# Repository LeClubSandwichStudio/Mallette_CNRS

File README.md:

# Mallette_CNRS
Water Analyser Briefcase for scientist
> ### Description

> ### [3D View](https://a360.co/3F3qp8W) - models designed by Mathorel Remi (2021)

# Key Features
> ### Hardware

* Protection Case : 
  * Case : [Pelican 1200](https://www.pelican.com/us/en/product/cases/protector/1200) 
  * Panel Frame : [Pelican 1200PF](https://www.pelican.com/us/en/accessory/cases/special-application-panel-frame/1200pf)
* MCU : [Teensy 3.6](https://www.pjrc.com/store/teensy36.html)
* OS : Raspberry Pi 4B - [RaspOS](https://www.raspberrypi.org/software/)
* Sensors : 
  * PH : [SEN0161-V2](https://wiki.dfrobot.com/Gravity__Analog_pH_Sensor_Meter_Kit_V2_SKU_SEN0161-V2)
  * EC : [DFR0300](https://wiki.dfrobot.com/Gravity__Analog_Electrical_Conductivity_Sensor___Meter_V2__K=1__SKU_DFR0300)
  * Temperature
  * Turbidity

> ### Software

# Summary

# Licence

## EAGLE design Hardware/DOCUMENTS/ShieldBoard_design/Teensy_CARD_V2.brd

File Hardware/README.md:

# Bill Of Materials

> MCU
- [Teensy 3.6](https://www.pjrc.com/store/teensy36.html)

> OS
- [Raspberry Pi 4B](https://www.raspberrypi.org/products/raspberry-pi-4-model-b/)

> Sensors
- [DFRobot Analog Turbidity Sensor](https://wiki.dfrobot.com/Turbidity_sensor_SKU__SEN0189)
- [DFRobot Analog EC Meter V2](https://wiki.dfrobot.com/Gravity__Analog_Electrical_Conductivity_Sensor___Meter_V2__K=1__SKU_DFR0300)
- [DFRobot Analog PH Meter V2](https://wiki.dfrobot.com/Gravity__Analog_pH_Sensor_Meter_Kit_V2_SKU_SEN0161-V2)
- [DFRobot Digital Temperature Sensor](https://wiki.dfrobot.com/Waterproof_DS18B20_Digital_Temperature_Sensor__SKU_DFR0198_)

> Shield
- Custom LCSS Teensy Shield

https://a360.co/3LIjGnY

> Others
- Li-Ion Charger
- Li-Iion Battery
- I/O Switch
- Status Led
-

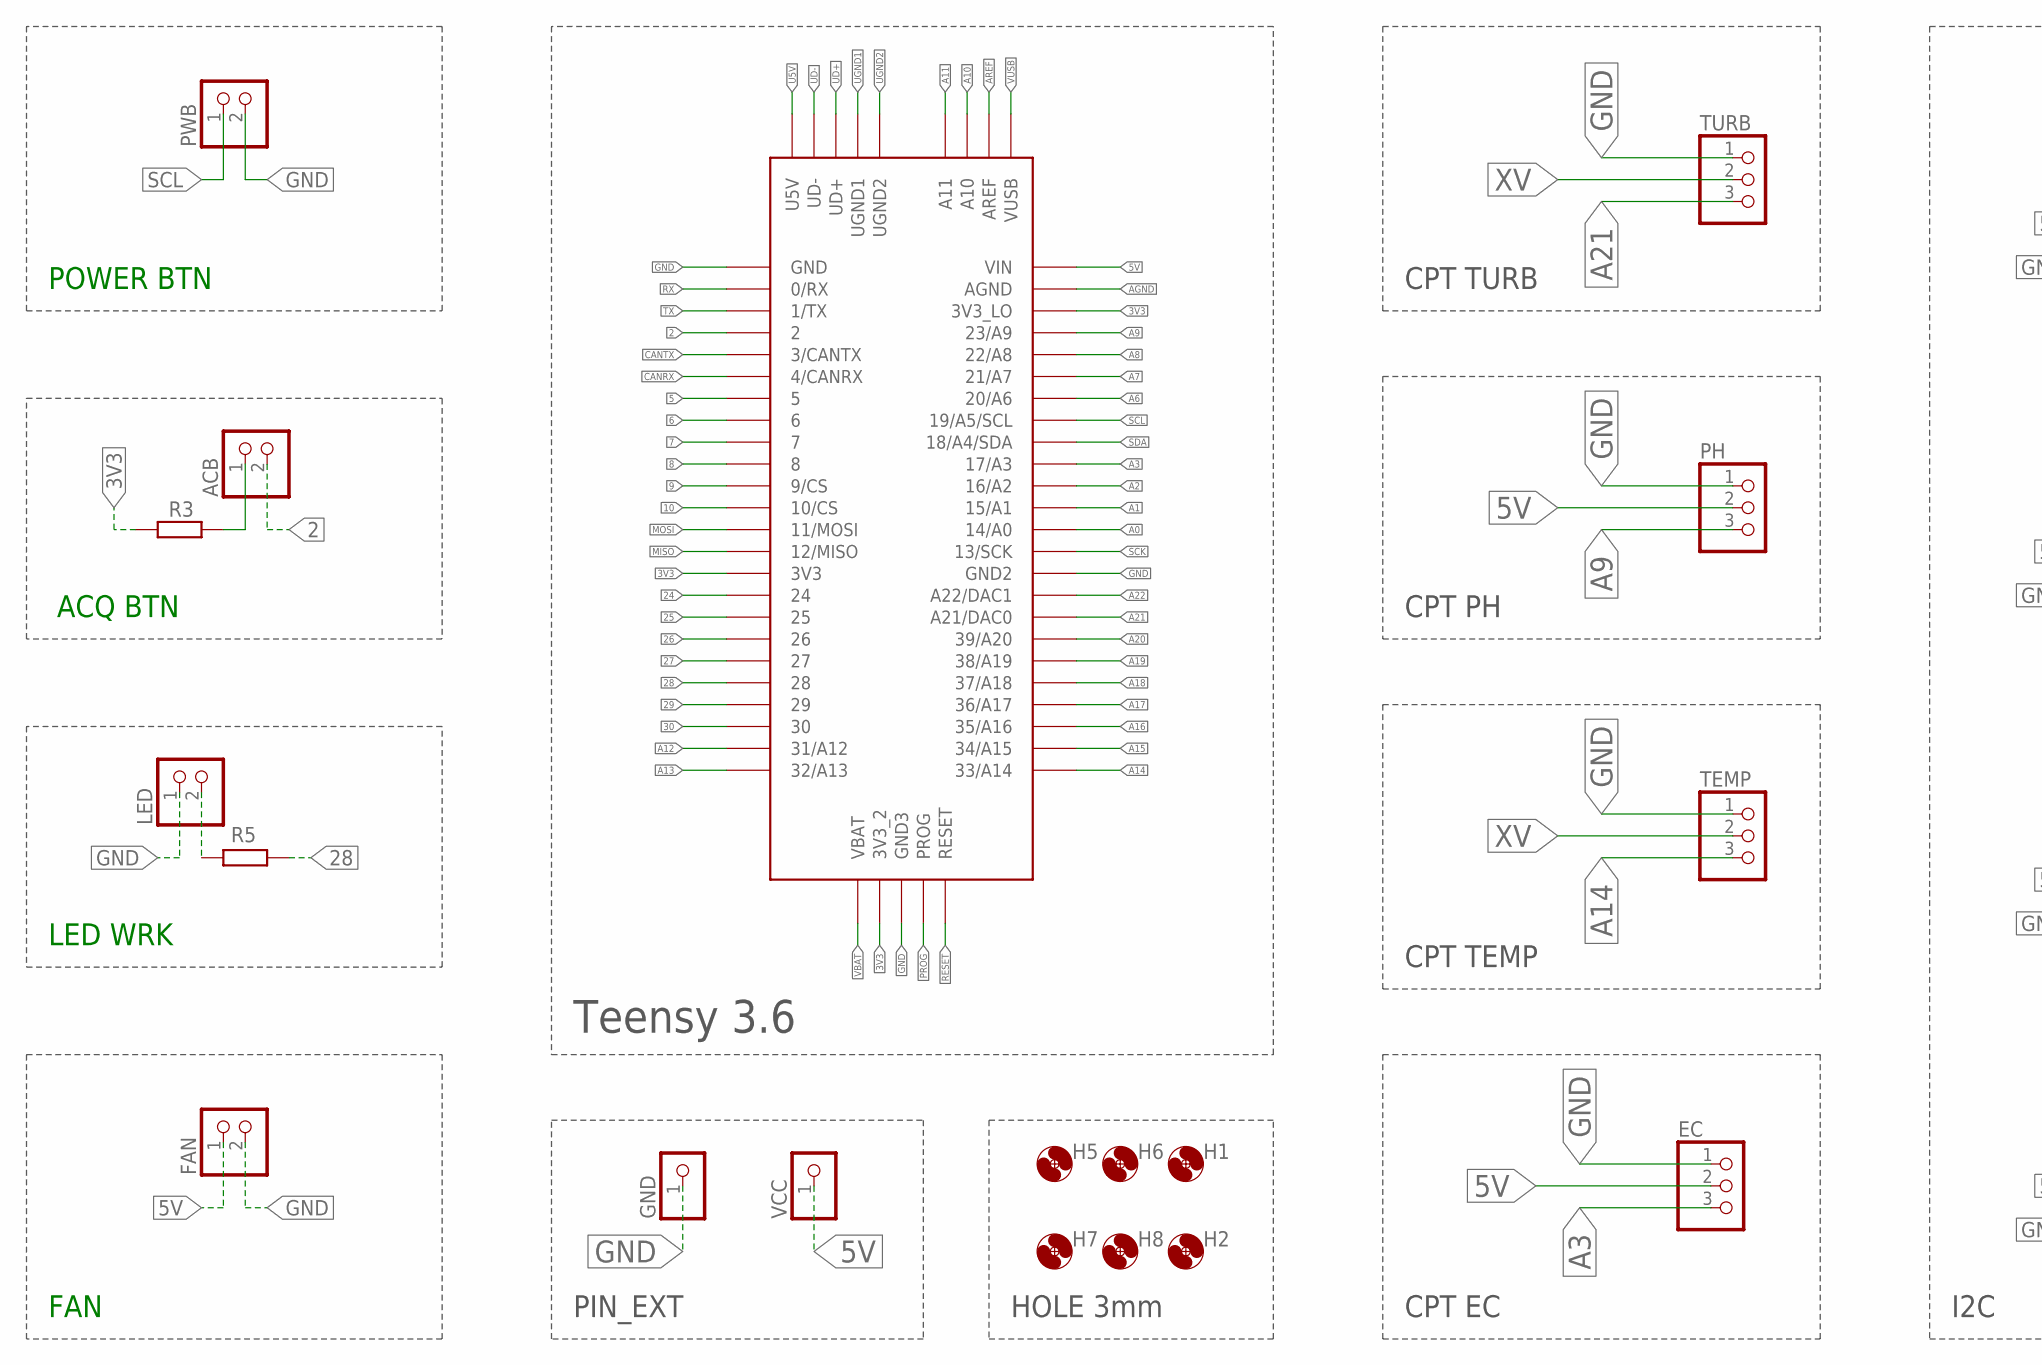
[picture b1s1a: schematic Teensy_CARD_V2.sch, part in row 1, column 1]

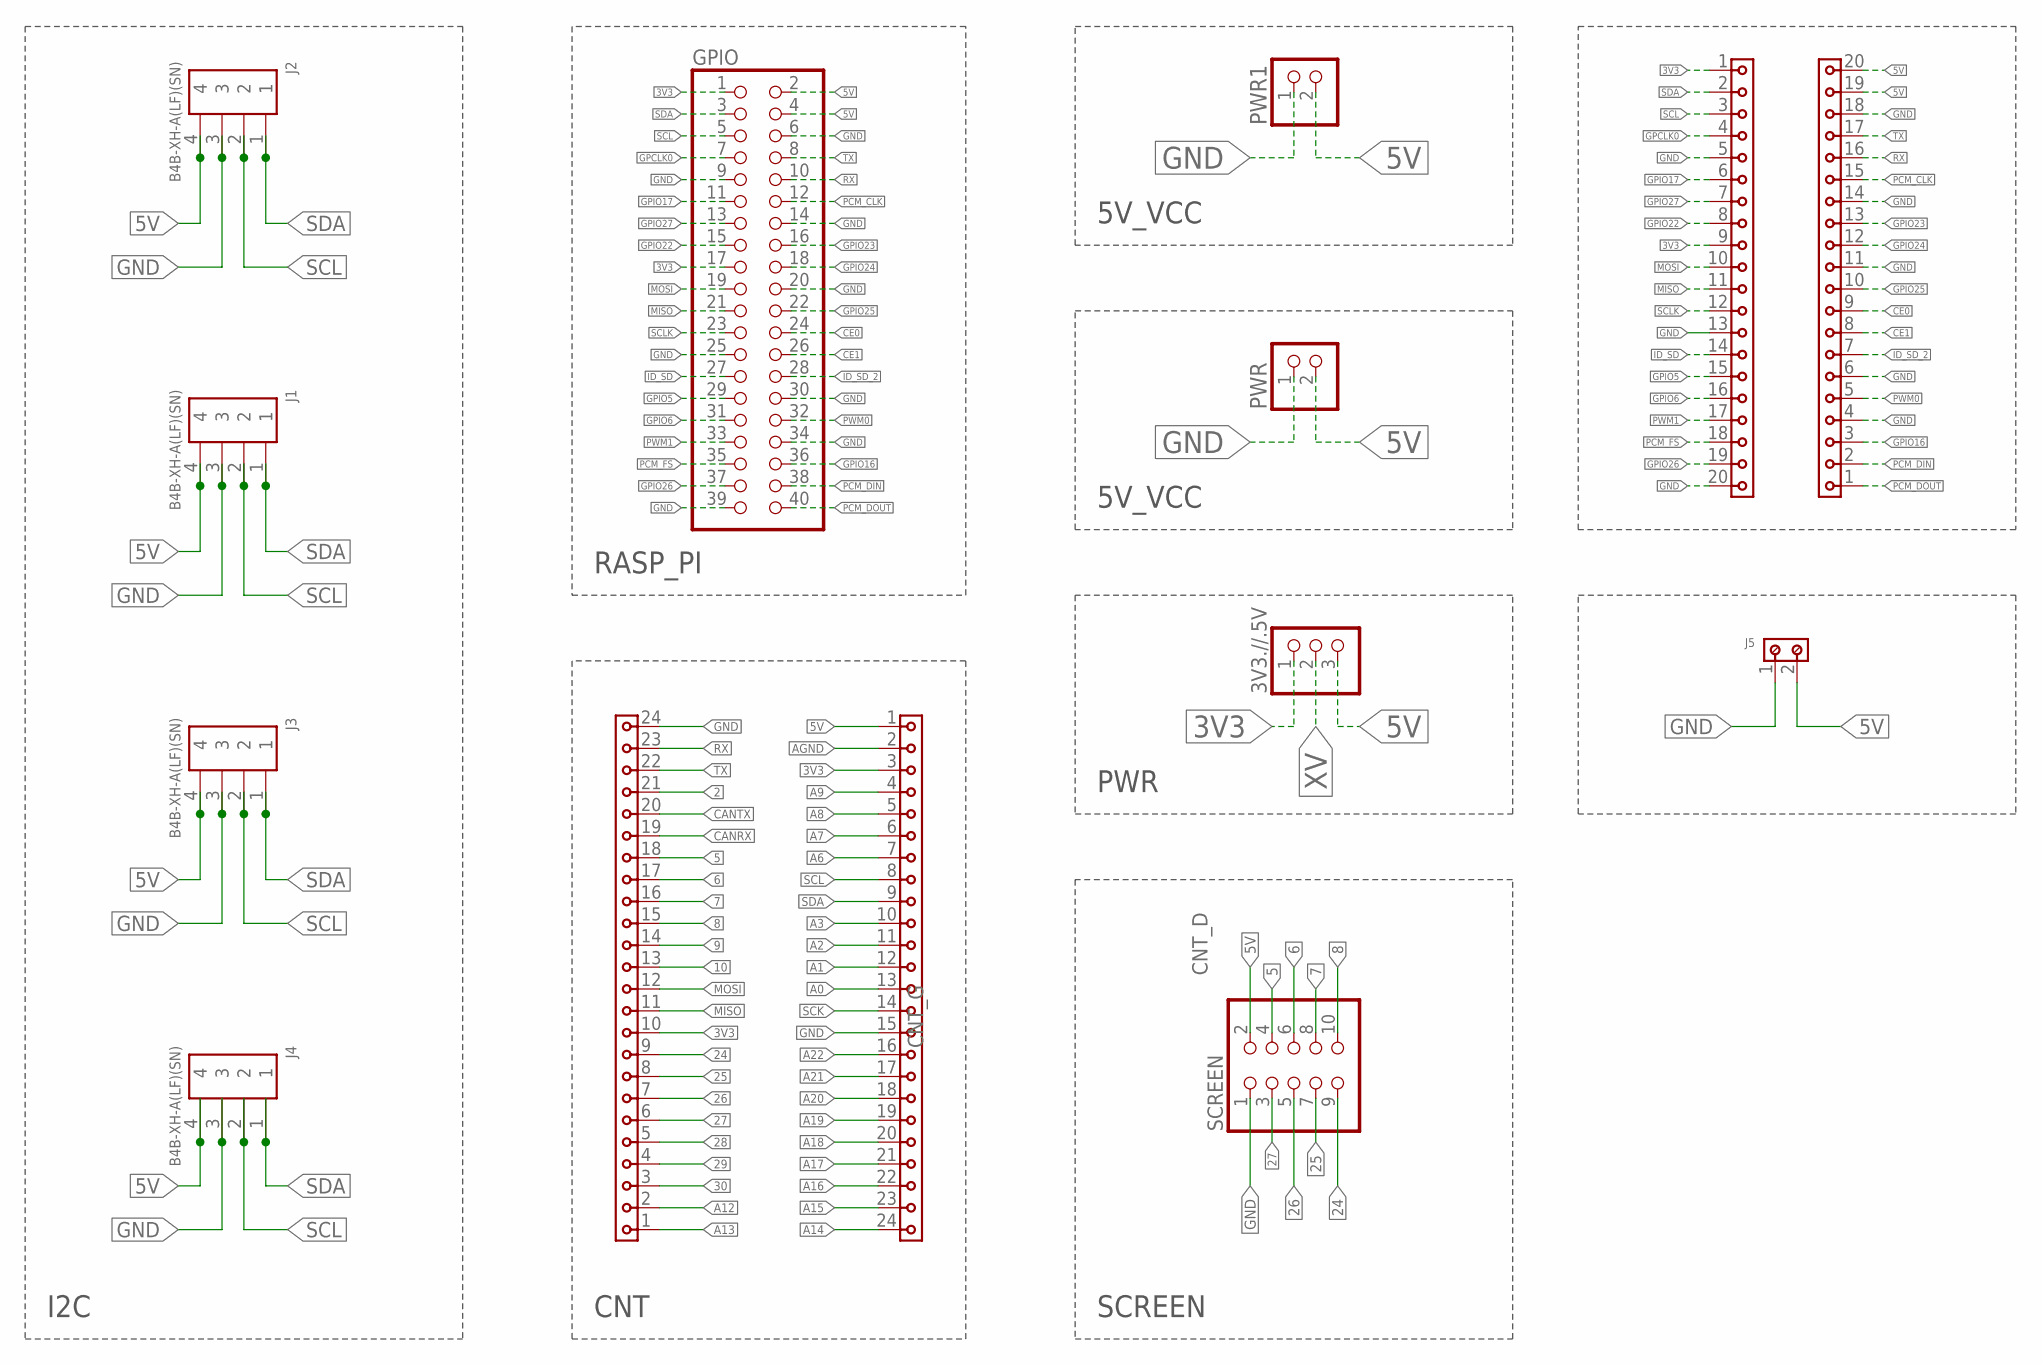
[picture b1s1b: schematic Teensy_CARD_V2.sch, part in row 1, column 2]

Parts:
3V3.//.5V: PINHD-1X3; 1X03
ACB: PINHD-1X2; 1X02
CNT_D: 6130XX11821_61302411821; 61302411821
CNT_G: 6130XX11821_61302411821; 61302411821
EC: PINHD-1X3; 1X03
FAN: PINHD-1X2; 1X02
GND: PINHD-1X1; 1X01
GPIO: PINHD-2X20; 2X20
H1, H2, H5, H6, H7, H8: MOUNT-HOLE3.0; 3,0
J1, J2, J3, J4: B4B-XH-A(LF)(SN)
J5: 691213510002
JP1, JP2: 6130XX11821_61302011821; 61302011821
LED: PINHD-1X2; 1X02
PH: PINHD-1X3; 1X03
PWB: PINHD-1X2; 1X02
PWR, PWR1: PINHD-1X2; 1X02
R3, R5: R-EU_0207/10; 0207/10
SCREEN: PINHD-2X5; 2X05
TEMP: PINHD-1X3; 1X03
TURB: PINHD-1X3; 1X03
U$1: TEENSY_3.5/3.6
VCC: PINHD-1X1; 1X01

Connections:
2: ACB.2, CNT_G.21, U$1.2
3V3: 3V3.//.5V.1, CNT_D.3, CNT_G.10, GPIO.1, GPIO.17, JP1.1, JP1.9, R3.1, U$1.3V3, U$1.3V3_2, U$1.3V3_LO
5: CNT_G.18, SCREEN.4, U$1.5
5V: 3V3.//.5V.3, CNT_D.1, EC.2, FAN.1, GPIO.2, GPIO.4, J1.4, J2.4, J3.4, J4.4, J5.2, JP2.19, JP2.20, PH.2, PWR.2, PWR1.2, SCREEN.2, U$1.VIN, VCC.1
6: CNT_G.17, SCREEN.6, U$1.6
7: CNT_G.16, SCREEN.8, U$1.7
8: CNT_G.15, SCREEN.10, U$1.8
9: CNT_G.14, U$1.9/CS
10: CNT_G.13, U$1.10/CS
24: CNT_G.9, SCREEN.9, U$1.24
25: CNT_G.8, SCREEN.7, U$1.25
26: CNT_G.7, SCREEN.5, U$1.26
27: CNT_G.6, SCREEN.3, U$1.27
28: CNT_G.5, R5.1, U$1.28
29: CNT_G.4, U$1.29
30: CNT_G.3, U$1.30
A0: CNT_D.13, U$1.14/A0
A1: CNT_D.12, U$1.15/A1
A2: CNT_D.11, U$1.16/A2
A3: CNT_D.10, EC.3, U$1.17/A3
A6: CNT_D.7, U$1.20/A6
A7: CNT_D.6, U$1.21/A7
A8: CNT_D.5, U$1.22/A8
A9: CNT_D.4, PH.3, U$1.23/A9
A10: U$1.A10
A11: U$1.A11
A12: CNT_G.2, U$1.31/A12
A13: CNT_G.1, U$1.32/A13
A14: CNT_D.24, TEMP.3, U$1.33/A14
A15: CNT_D.23, U$1.34/A15
A16: CNT_D.22, U$1.35/A16
A17: CNT_D.21, U$1.36/A17
A18: CNT_D.20, U$1.37/A18
A19: CNT_D.19, U$1.38/A19
A20: CNT_D.18, U$1.39/A20
A21: CNT_D.17, TURB.3, U$1.21/DAC0 (A21/DAC0)
A22: CNT_D.16, U$1.A22/DAC1
AGND: CNT_D.2, U$1.AGND
AREF: U$1.AREF
CANRX: CNT_G.19, U$1.4/CANRX
CANTX: CNT_G.20, U$1.3/CANTX
CE0: GPIO.24, JP2.9
CE1: GPIO.26, JP2.8
GND: CNT_D.15, CNT_G.24, EC.1, FAN.2, GND.1, GPIO.6, GPIO.9, GPIO.14, GPIO.20, GPIO.25, GPIO.30, GPIO.34, GPIO.39, J1.3, J2.3, J3.3, J4.3, J5.1, JP1.5, JP1.13, JP1.20, JP2.4, JP2.6, JP2.11, JP2.14, JP2.18, LED.1, PH.1, PWB.2, PWR.1, PWR1.1, SCREEN.1, TEMP.1, TURB.1, U$1.GND, U$1.GND2, U$1.GND3
GPCLK0: GPIO.7, JP1.4
GPIO5: GPIO.29, JP1.15
GPIO6: GPIO.31, JP1.16
GPIO16: GPIO.36, JP2.3
GPIO17: GPIO.11, JP1.6
GPIO22: GPIO.15, JP1.8
GPIO23: GPIO.16, JP2.13
GPIO24: GPIO.18, JP2.12
GPIO25: GPIO.22, JP2.10
GPIO26: GPIO.37, JP1.19
GPIO27: GPIO.13, JP1.7
ID_SD: GPIO.27, JP1.14
ID_SD_2: GPIO.28, JP2.7
MISO: CNT_G.11, GPIO.21, JP1.11, U$1.12/MISO
MOSI: CNT_G.12, GPIO.19, JP1.10, U$1.11/MOSI
unnamed: ACB.1, R3.2
unnamed: LED.2, R5.2
PCM_CLK: GPIO.12, JP2.15
PCM_DIN: GPIO.38, JP2.2
PCM_DOUT: GPIO.40, JP2.1
PCM_FS: GPIO.35, JP1.18
PROG: U$1.PROG
PWM0: GPIO.32, JP2.5
PWM1: GPIO.33, JP1.17
RESET: U$1.RESET
RX: CNT_G.23, GPIO.10, JP2.16, U$1.0/RX
SCK: CNT_D.14, U$1.13/SCK
SCL: CNT_D.8, GPIO.5, J1.2, J2.2, J3.2, J4.2, JP1.3, PWB.1, U$1.19/A5/SCL
SCLK: GPIO.23, JP1.12
SDA: CNT_D.9, GPIO.3, J1.1, J2.1, J3.1, J4.1, JP1.2, U$1.18/A4/SDA
TX: CNT_G.22, GPIO.8, JP2.17, U$1.1/TX
U5V: U$1.U5V
UD+: U$1.UD+
UD-: U$1.UD-
UGND1: U$1.UGND1
UGND2: U$1.UGND2
VBAT: U$1.VBAT
VUSB: U$1.VUSB
XV: 3V3.//.5V.2, TEMP.2, TURB.2

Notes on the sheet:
Teensy 3.6
CPT TEMP
CPT PH
CPT TURB
CPT EC
HOLE 3mm
PWR
CNT
5V_VCC
PIN_EXT
RASP_PI
I2C
SCREEN
FAN
POWER BTN
ACQ BTN
LED WRK

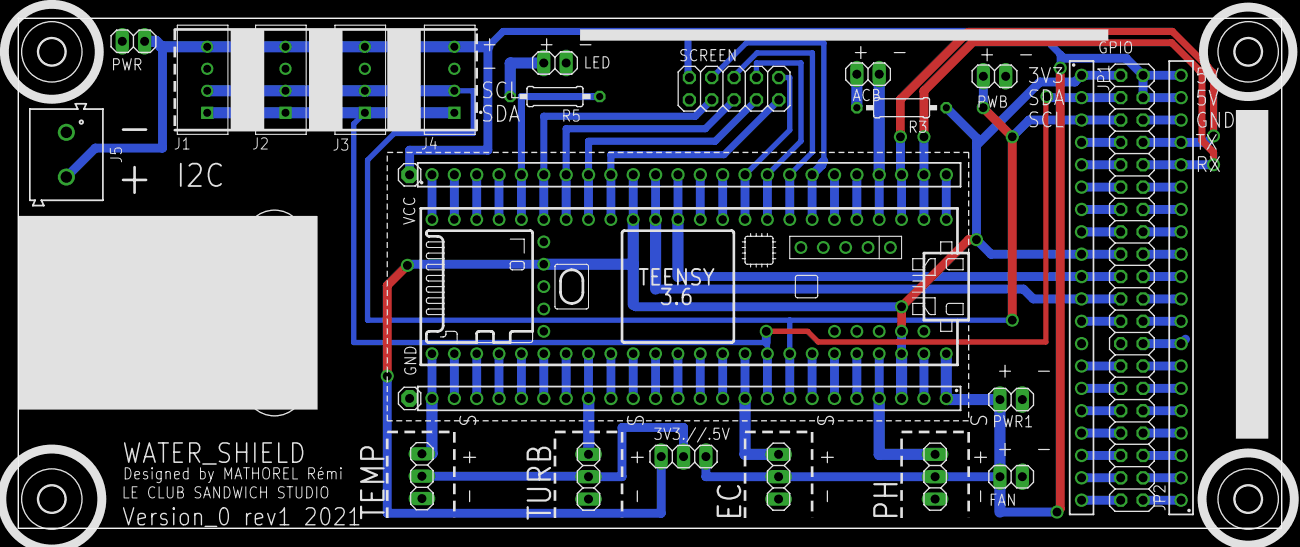
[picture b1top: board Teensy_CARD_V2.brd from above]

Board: 2 copper layers, 143.5 x 57.9 mm, 33 parts (0 on the bottom side), 71 nets.

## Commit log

2021-06-23 Create Water_Analyser_Briefcase___16Bits
2021-06-23 Rename Water_Analyser_Briefcase___16Bits to Water_Analyser_Briefcase___16Bits.ino
2021-07-15 General_Review___code
    - erase old folder
    - update Arduino code
2021-07-15 Add Raspi contents
    - www folder
    - main.py
    - lancement.sh
    Clean a lot of demo files
2021-07-15 Working version
2021-07-16 Inverse Turbidity/EC in JSON
2021-07-16 Inverse in cards Turb/EC in main.js
2021-07-22 Add desktop arduino folder
2021-07-24 Add RTC Time feature
    Basic use with Teensy example
2021-07-24 Update Logs files and others
    - Change logs name iteration (date > number) to avoid any issue with non synchronisation date and time
    - Change save button alignment
    - Delete useless demo files from template
2021-07-29 Add voltage values in JSON
    - Add voltages values for PH, EC, turbidity
    - Update decimal values for each
2022-02-17 Create LCD.ino
    add unverified demo code to test LCD
2022-02-17 Update LCD.ino
    ADD link to ADC buttons control forum
2022-02-17 Add Watercase dedicated code (x10)
2022-02-17 change 2021 cnrs code location
2022-02-17 Update README.md
    add 3D shared model shield
2022-02-17 add teensy shield board files
    add SCH + BRD shield V2 reviewed by Simon JUIF 09/2021
2022-02-17 shield board updates
    updates eagle files teensy board
2022-04-04 cleanup
    Move and clean folders
2022-05-05 Updates Hardware and Arduino features
    * v1.3.2 :
    * BIG UPDATES
    * > add LBO control to check battery status
    * > add battery check during setup & loop
    * GLOBAL CHANGES
    * > clean some lines
2022-05-05 organize folder and version
2022-05-05 Add pdf manuals
2022-05-05 Change pdf names
2022-05-05 Add EC and PH calibration serial commands

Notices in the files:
parts and their libraries:
Wurth_Connectors_WR-TBL Rising Cage Clam: Copyright: Würth Elektronik
